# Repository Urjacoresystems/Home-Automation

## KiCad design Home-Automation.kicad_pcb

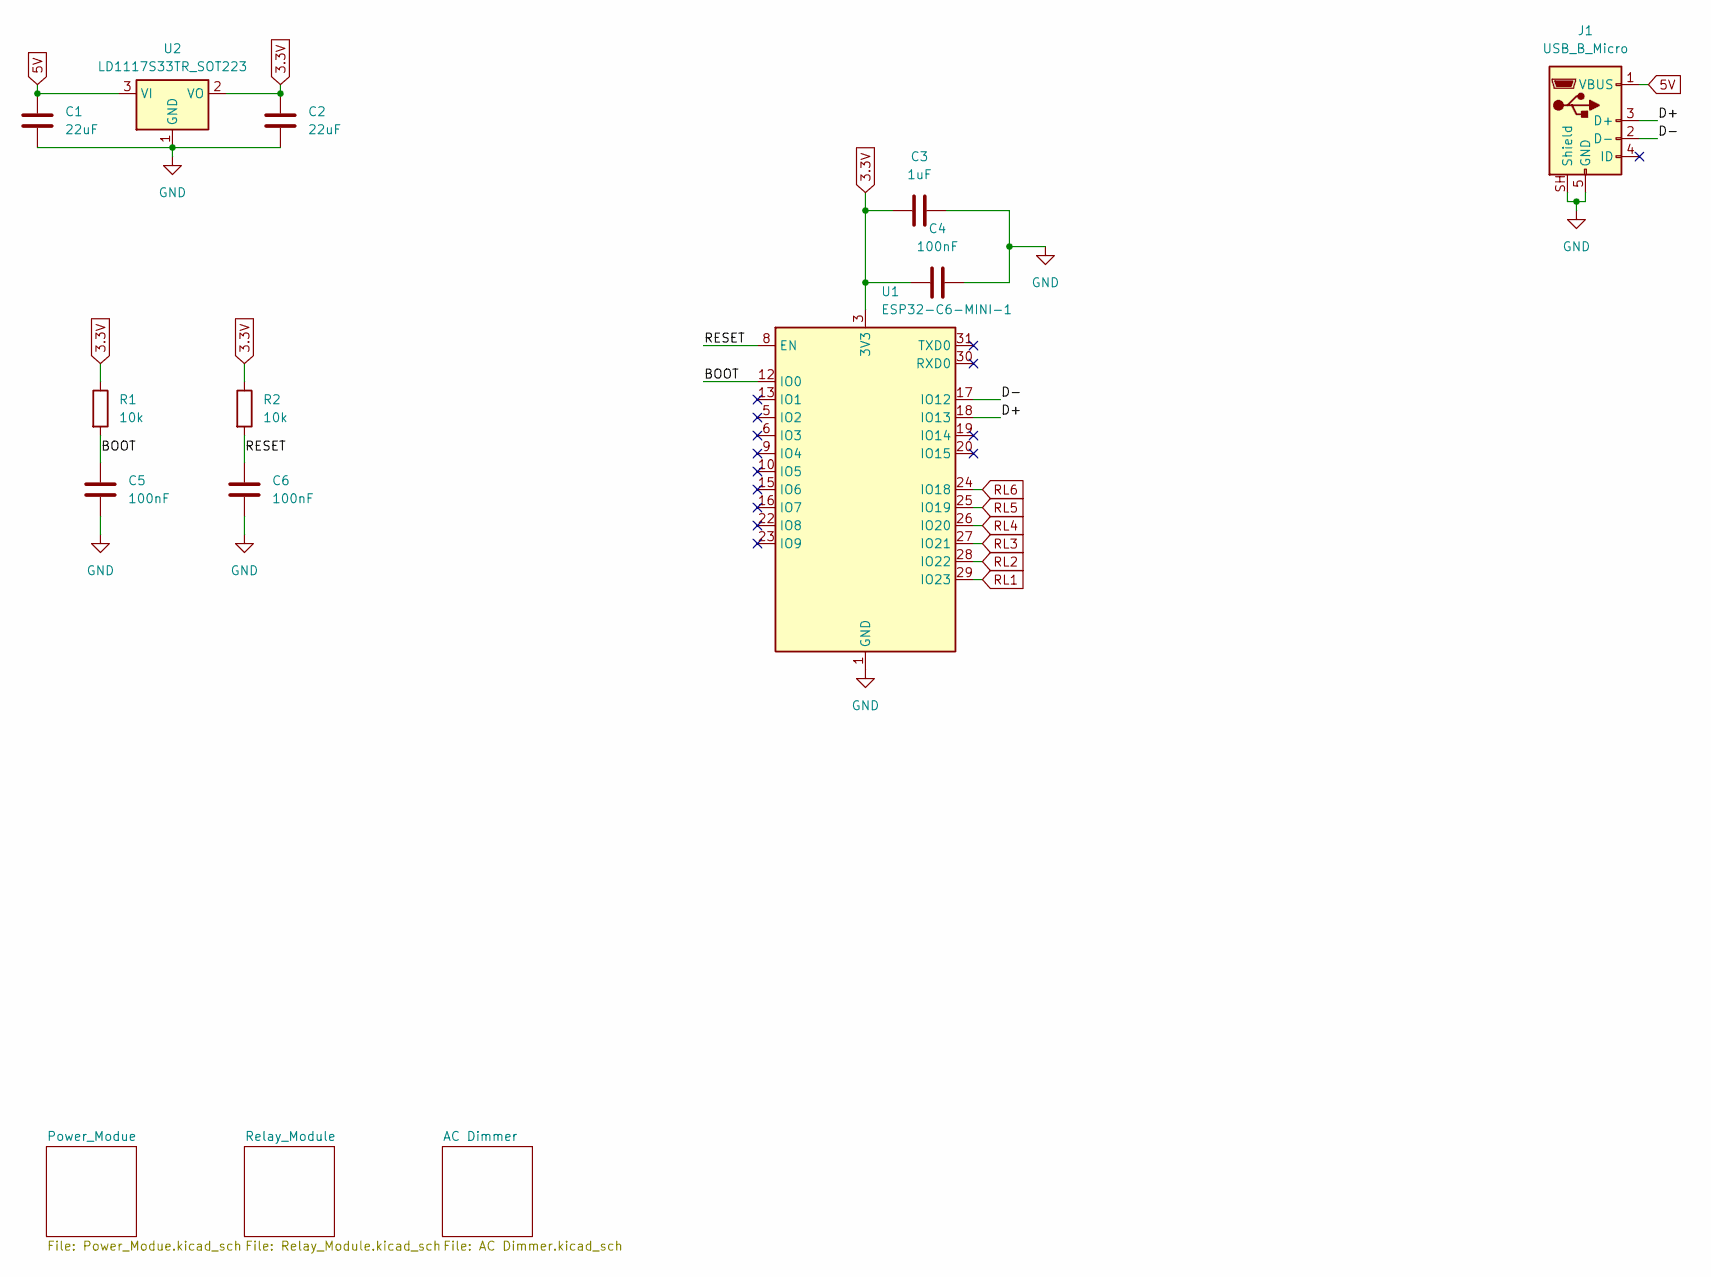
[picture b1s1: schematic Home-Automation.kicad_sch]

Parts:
C1, C2: 22uF; C_0603_1608Metric
C3: 1uF; C_0603_1608Metric
C4, C5, C6: 100nF; C_0603_1608Metric
J1: USB_B_Micro; USB_Micro-B_Amphenol_10118193-0001LF_Horizontal
R1, R2: 10k; R_0603_1608Metric
U1: ESP32-C6-MINI-1
U2: LD1117S33TR_SOT223; SOT-223-3_TabPin2

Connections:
3.3V: C2.1, C3.1, C4.1, R1.1, R2.1, U1.3 (3V3), U2.2 (VO)
5V: C1.1, J1.1 (VBUS), U2.3 (VI); also elsewhere on the board
/BOOT: C5.2, R1.2, U1.12 (IO0)
/D+: J1.3 (D+), U1.18 (IO13)
/D-: J1.2 (D-), U1.17 (IO12)
/RESET: C6.2, R2.2, U1.8 (EN)
GND: C1.2, C2.2, C3.2, C4.2, C5.1, C6.1, J1.5 (GND), J1.SH (Shield), U1.1 (GND), U1.2 (GND), U1.11 (GND), U1.14 (GND), U1.36 (GND), U1.37 (GND), U1.38 (GND), U1.39 (GND), U1.40 (GND), U1.41 (GND), U1.42 (GND), U1.43 (GND), U1.44 (GND), U1.45 (GND), U1.46 (GND), U1.47 (GND), U1.48 (GND), U1.49 (GND), U1.50 (GND), U1.51 (GND), U1.52 (GND), U1.53 (GND), U2.1 (GND); also elsewhere on the board
RL1: U1.29 (IO23); also elsewhere on the board
RL2: U1.28 (IO22); also elsewhere on the board
RL3: U1.27 (IO21); also elsewhere on the board
RL4: U1.26 (IO20); also elsewhere on the board
RL5: U1.25 (IO19); also elsewhere on the board
RL6: U1.24 (IO18); also elsewhere on the board

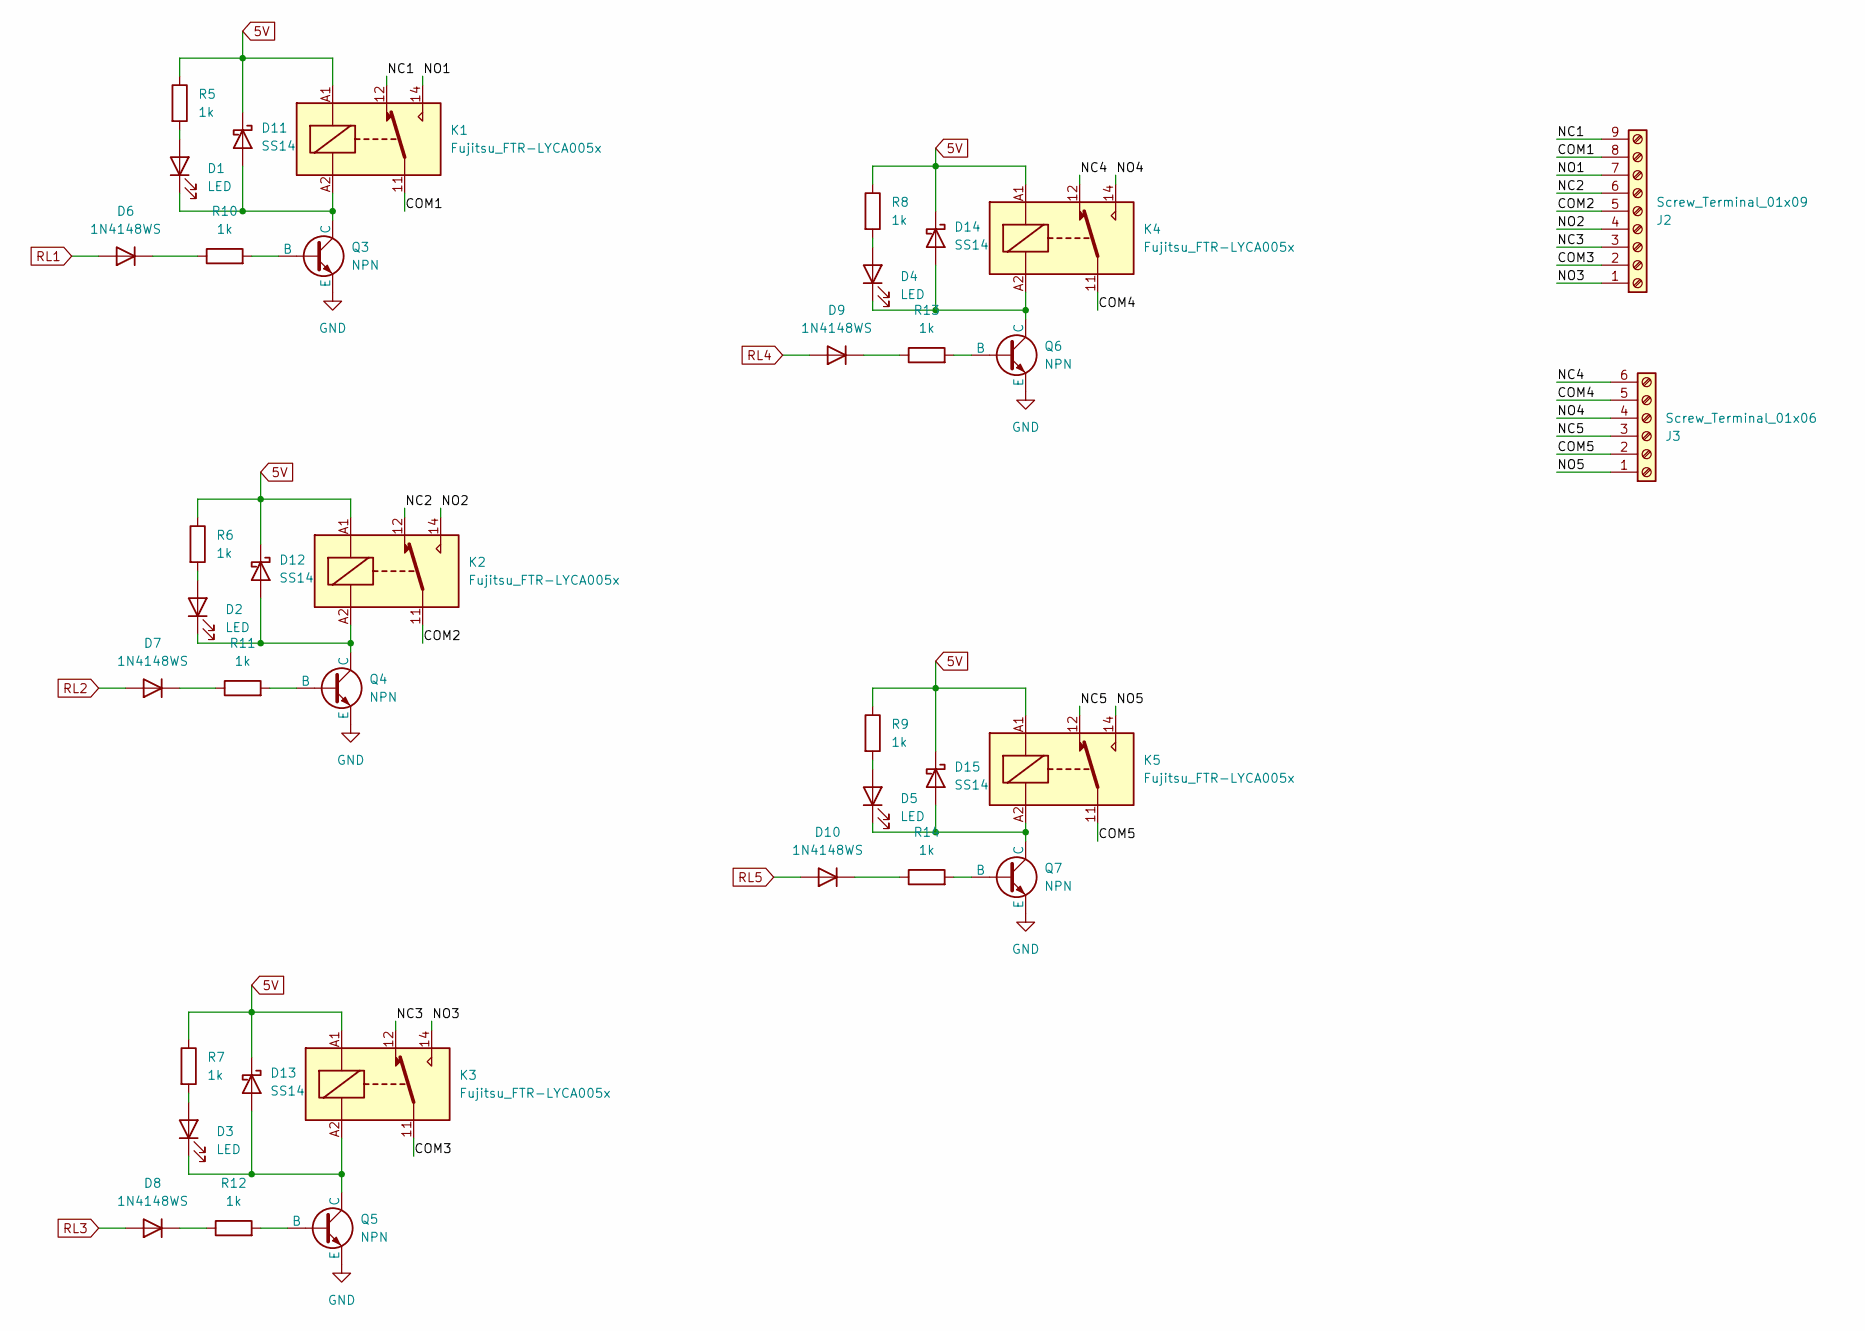
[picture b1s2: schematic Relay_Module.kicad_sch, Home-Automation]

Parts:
D1, D2, D3, D4, D5: LED; LED_0603_1608Metric
D6, D7, D8, D9, D10: 1N4148WS; D_SOD-323
D11, D12, D13, D14, D15: SS14; D_SMA
J2: Screw_Terminal_01x09; TerminalBlock_4Ucon_1x09_P3.50mm_Vertical
J3: Screw_Terminal_01x06; TerminalBlock_4Ucon_1x06_P3.50mm_Vertical
K1, K2, K3, K4, K5: Fujitsu_FTR-LYCA005x; Relay_SPDT_Fujitsu_FTR-LYCA005x_FormC_Vertical
Q3, Q4, Q5, Q6, Q7: NPN; SOT-23
R5, R6, R7, R8, R9, R10, R11, R12, R13, R14: 1k; R_0603_1608Metric

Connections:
5V: D11.1 (K), D12.1 (K), D13.1 (K), D14.1 (K), D15.1 (K), K1.A1, K2.A1, K3.A1, K4.A1, K5.A1, R5.1, R6.1, R7.1, R8.1, R9.1; also elsewhere on the board
/Relay_Module/COM1: J2.8, K1.11
/Relay_Module/COM2: J2.5, K2.11
/Relay_Module/COM3: J2.2, K3.11
/Relay_Module/COM4: J3.5, K4.11
/Relay_Module/COM5: J3.2, K5.11
/Relay_Module/NC1: J2.9, K1.12
/Relay_Module/NC2: J2.6, K2.12
/Relay_Module/NC3: J2.3, K3.12
/Relay_Module/NC4: J3.6, K4.12
/Relay_Module/NC5: J3.3, K5.12
/Relay_Module/NO1: J2.7, K1.14
/Relay_Module/NO2: J2.4, K2.14
/Relay_Module/NO3: J2.1, K3.14
/Relay_Module/NO4: J3.4, K4.14
/Relay_Module/NO5: J3.1, K5.14
GND: Q3.2 (E), Q4.2 (E), Q5.2 (E), Q6.2 (E), Q7.2 (E); also elsewhere on the board
unnamed: D1.2 (A), R5.2
unnamed: D1.1 (K), D11.2 (A), K1.A2, Q3.3 (C)
unnamed: D2.2 (A), R6.2
unnamed: D3.2 (A), R7.2
unnamed: D4.2 (A), R8.2
unnamed: D5.2 (A), R9.2
unnamed: D6.1 (K), R10.1
unnamed: D7.1 (K), R11.1
unnamed: D8.1 (K), R12.1
unnamed: D9.1 (K), R13.1
unnamed: D10.1 (K), R14.1
unnamed: D2.1 (K), D12.2 (A), K2.A2, Q4.3 (C)
unnamed: D3.1 (K), D13.2 (A), K3.A2, Q5.3 (C)
unnamed: D4.1 (K), D14.2 (A), K4.A2, Q6.3 (C)
unnamed: D5.1 (K), D15.2 (A), K5.A2, Q7.3 (C)
unnamed: Q3.1 (B), R10.2
unnamed: Q4.1 (B), R11.2
unnamed: Q5.1 (B), R12.2
unnamed: Q6.1 (B), R13.2
unnamed: Q7.1 (B), R14.2
RL1: D6.2 (A); also elsewhere on the board
RL2: D7.2 (A); also elsewhere on the board
RL3: D8.2 (A); also elsewhere on the board
RL4: D9.2 (A); also elsewhere on the board
RL5: D10.2 (A); also elsewhere on the board

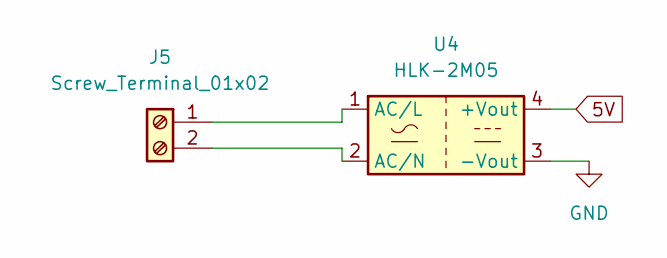
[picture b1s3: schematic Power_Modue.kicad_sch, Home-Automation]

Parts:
J5: Screw_Terminal_01x02; TerminalBlock_4Ucon_1x02_P3.50mm_Horizontal
U4: HLK-2M05; Converter_ACDC_Hi-Link_HLK-2Mxx

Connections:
5V: U4.4 (+Vout); also elsewhere on the board
GND: U4.3 (-Vout); also elsewhere on the board
unnamed: J5.1, U4.1 (AC/L)
unnamed: J5.2, U4.2 (AC/N)

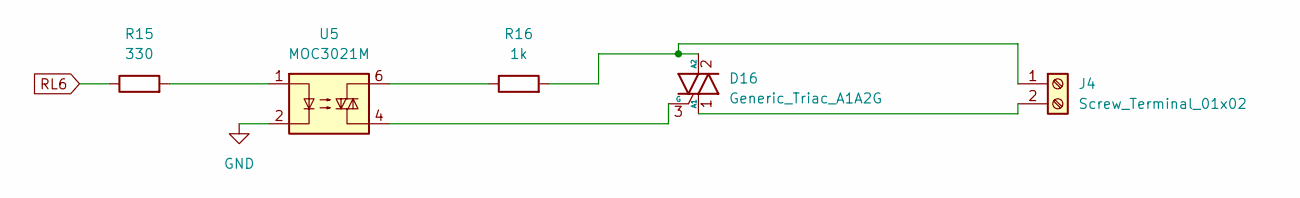
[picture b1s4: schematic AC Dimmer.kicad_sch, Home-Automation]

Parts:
D16: Generic_Triac_A1A2G; TO-220-3_Vertical
J4: Screw_Terminal_01x02; TerminalBlock_4Ucon_1x02_P3.50mm_Horizontal
R15: 330; R_0603_1608Metric
R16: 1k; R_0603_1608Metric
U5: MOC3021M; SMDIP-6_W7.62mm

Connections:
GND: U5.2; also elsewhere on the board
unnamed: D16.1 (A1), J4.2
unnamed: D16.2 (A2), J4.1, R16.2
unnamed: D16.3 (G), U5.4
unnamed: R15.2, U5.1
unnamed: R16.1, U5.6
RL6: R15.1; also elsewhere on the board

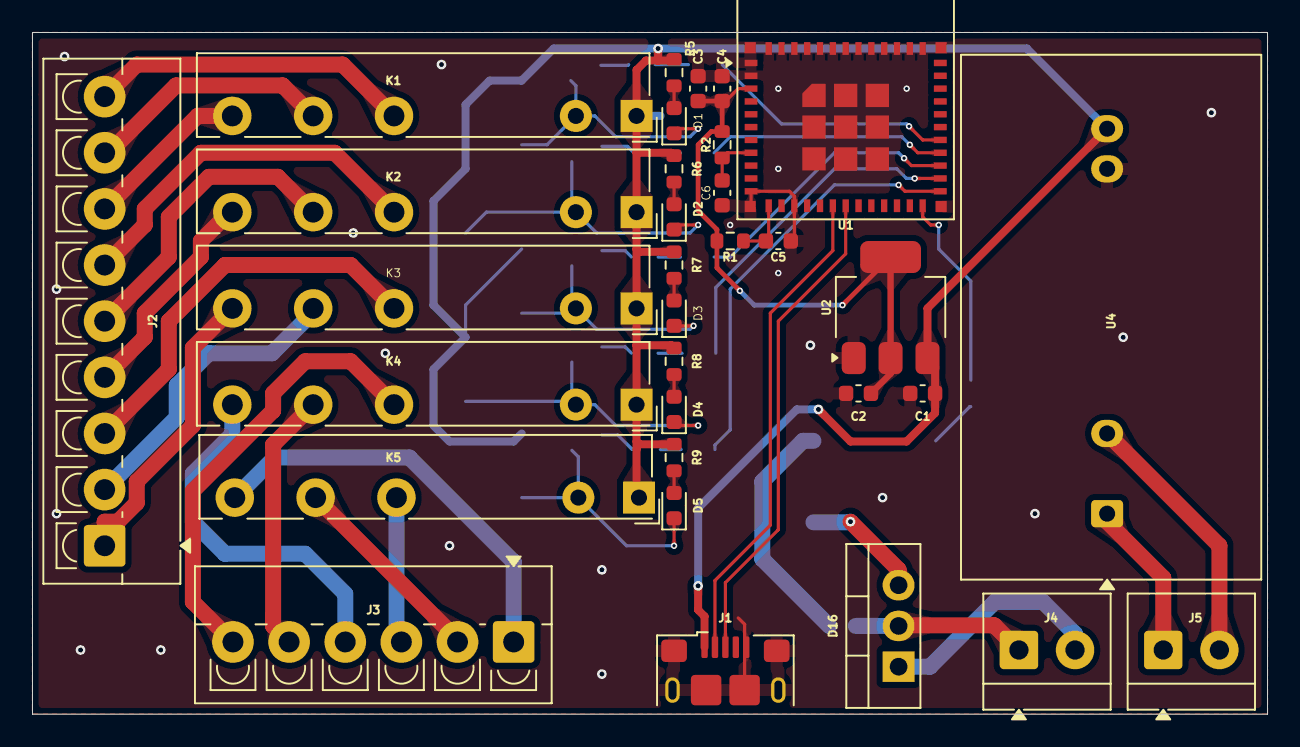
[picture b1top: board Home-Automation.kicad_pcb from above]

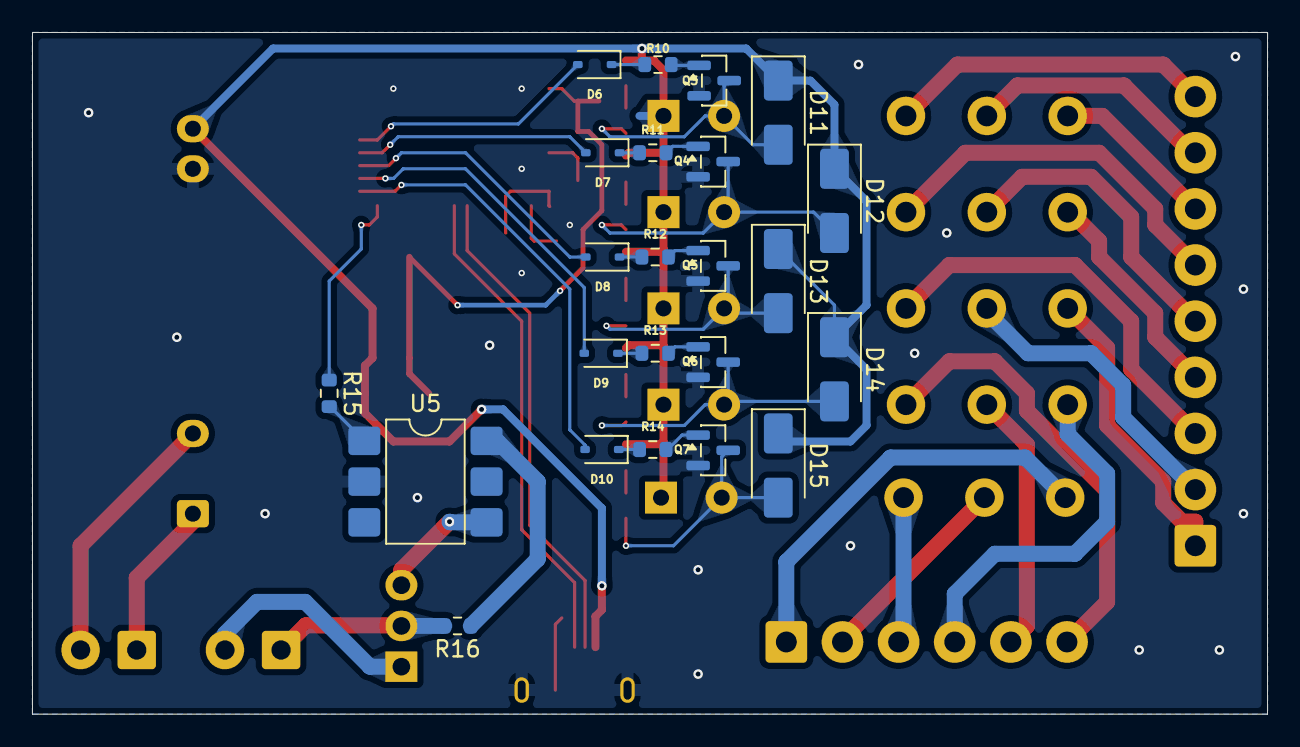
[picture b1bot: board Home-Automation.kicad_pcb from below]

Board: 2 copper layers, 77.0 x 42.5 mm, 55 parts (23 on the bottom side), 55 nets.
